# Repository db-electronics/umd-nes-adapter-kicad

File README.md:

# Copyright and Disclaimer
Copyright: René Richard

This documentation describes Open Hardware and is licensed under the
CERN OHL v. 1.2.

You may redistribute and modify this documentation under the terms of the
CERN OHL v.1.2. (http://ohwr.org/cernohl). This documentation is distributed
WITHOUT ANY EXPRESS OR IMPLIED WARRANTY, INCLUDING OF
MERCHANTABILITY, SATISFACTORY QUALITY AND FITNESS FOR A
PARTICULAR PURPOSE. Please see the CERN OHL v.1.2 for applicable
conditions

# NES UMD Adapters
This KiCad project contains the NES cartridge adapter for the [Universal Mega Dumper](https://github.com/db-electronics/Universal-Mega-Dumper).

## UMD ID
* 0x01

Each UMD adapter contains a serial shift register with an 8bit ID.

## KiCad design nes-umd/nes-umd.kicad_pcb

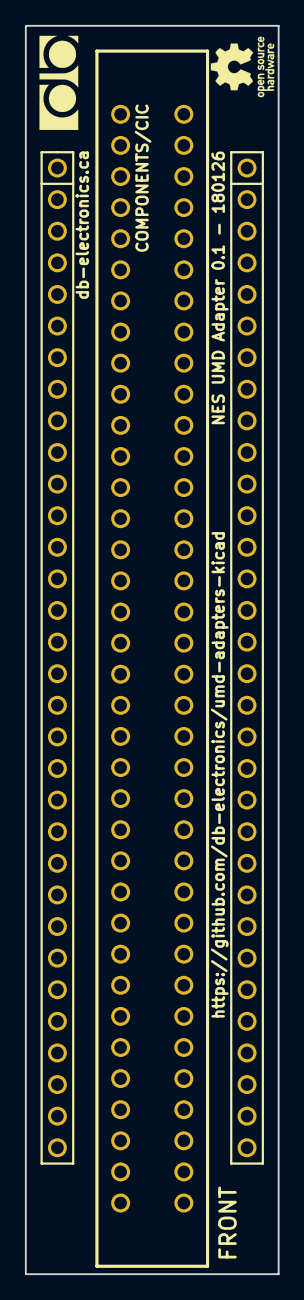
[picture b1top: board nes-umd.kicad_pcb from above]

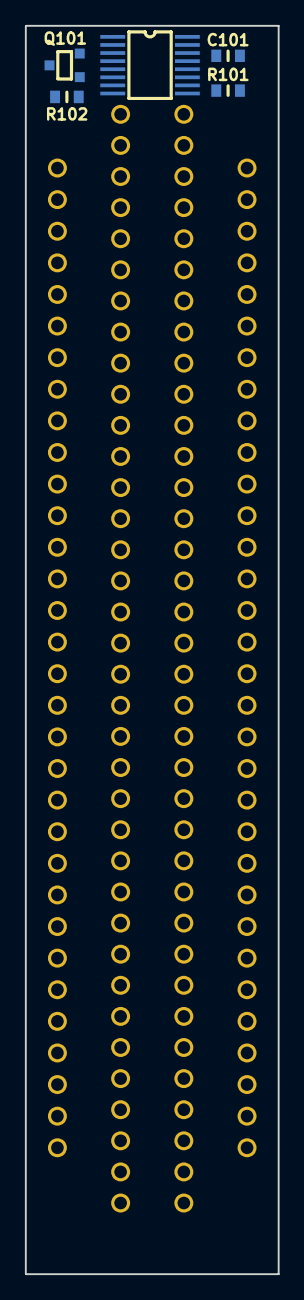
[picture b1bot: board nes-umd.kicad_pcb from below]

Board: 2 copper layers, 20.3 x 100.3 mm, 7 parts (5 on the bottom side), 33 nets, no tracks yet.

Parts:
C101: 0.1uF/50V; 0603
CON101: NES-CONN
CON102: UMD-CONN; UMD-CONN-DIP64
Q101: SMMBT3904LT1G; SOT23
R101, R102: 10k; 0603
U101: MC74HC589ADTR2G; TSSOP-16

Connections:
+5V: C101.2, CON101.36, CON102.10, CON102.31, CON102.34, R102.2, U101.7, U101.14, U101.16
/A0: CON101.13, CON101.29, CON102.46
/A1: CON101.12, CON101.28, CON102.43
/A2: CON101.11, CON101.27, CON102.42
/A3: CON101.10, CON101.26, CON102.39
/A4: CON101.9, CON101.25, CON102.26
/A5: CON101.8, CON101.24, CON102.23
/A6: CON101.7, CON101.23, CON102.22
/A7: CON101.6, CON101.59, CON102.19
/A8: CON101.5, CON101.60, CON102.54
/A9: CON101.4, CON101.61, CON102.51
/A10: CON101.3, CON101.63, CON102.50
/A11: CON101.2, CON101.62, CON102.47
/A12: CON101.39, CON101.64, CON102.18
/A13: CON101.40, CON102.15
/A14: CON101.41, CON102.14
/D0: CON101.30, CON101.49, CON102.45
/D1: CON101.31, CON101.48, CON102.44
/D2: CON101.32, CON101.47, CON102.41
/D3: CON101.33, CON101.46, CON102.40
/D4: CON101.45, CON101.69, CON102.25
/D5: CON101.44, CON101.68, CON102.24
/D6: CON101.43, CON101.67, CON102.21
/D7: CON101.42, CON101.66, CON102.20
/MISO: CON102.63, U101.9
/SCK: CON102.62, U101.11
/~ID: CON102.56, R101.2, U101.10
/~PCE: CON101.50, CON102.9
/~PWR: CON101.14, CON102.57
/~RST: CON102.58, U101.12
GND: C101.1, CON101.1, CON101.72, CON102.32, CON102.33, CON102.55, Q101.2, U101.1, U101.2, U101.3, U101.4, U101.5, U101.6, U101.8, U101.15
unnamed: Q101.1, R101.1
unnamed: Q101.3, R102.1, U101.13

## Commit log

2018-02-02 seperated SNES and NES into 2 repos
2018-02-02 fixed typo in readme
2018-03-14 added a few net labels
2018-03-15 schematic work
2018-03-21 adding shift register ID to schematic
2018-03-21 saved 1 pin on the ID function
2018-03-28 added v0.1 schematic
2018-03-28 parts placement for ID register

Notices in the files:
nes-umd/nes-umd.kicad_pcb:
Licensed under CERN OHL v.1.2
